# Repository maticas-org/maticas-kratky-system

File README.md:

# Maticas Kratky System 🌱

In this project we built a modified kratky system which consists of the usual bucket but now incorporates additional oxigenation with an oxigen pump, the idea behind this was to test the results of adding micorrizae to the water and keep it alive inside the kratky system with this additional aeration, comparisson tests still remain to be done yet, however we've got good results with our basil crop test.

### Results of the basil growing test

All the plants are showing a good root development.

And so far we've done 10 prunnings in about 2 months. It's true that we now have to develop a better concise and clear way to measure and compare results, but as far as building a system which allows plants to live with out concerning too much about taking care of the plants (5hr/month maximum) we've achived good results.

## Key features

- Capacity up to 8 plants with the current architecture for the growing system. 
- Measure ambient variables such as relative humidity and temperature, allows for extension and triggering of actions with this measurements.
- Control an AC actuator such as an oxigen pump _(We are expanding in order to control up to 3 AC actuators)._

- Local web server to monitor the conditions in the last 3 hours of operations of the device.
- Local web server available for modifying the periodicity and way the actuator works.
- Screen to display IP of the device in the local network and other desired data. 

<div style="display: flex; justify-content: center; align-items: center;">
  <div style="flex: 1; text-align: center; padding: 5px; height: auto; width: 45%;">
    
  </div>
  <div style="flex: 1; text-align: center; padding: 5px; height: auto; width: 45%;">
    
  </div>
</div>

## Notes over the development 📝

## Needed materials for replication ✅
### Structural materials

1. A pair of 20 liter containers [link to example product](https://articulo.mercadolibre.com.co/MCO-861436425-set-x-10-balde-cunete-20-litros-_JM#position=3&search_layout=stack&type=item&tracking_id=a9eae8bf-e021-4639-ab13-fa13d58bef19).

2. 8 cultivation baskets (or less depending on the space your plant needs) [link to reference product](https://www.amazon.com/Hydroponic-Plastic-Cultivation-Planting-Gardening/dp/B08R8LMF6L/ref=sr_1_2?crid=33OS09TYPPLFV&dib=eyJ2IjoiMSJ9.NfalgvycNBMZZM1CF_ESWtjJ-_G-A7rY25RSB5krQUKKu4zvjQOSep1QU8vNXbIBJZi8SxxX1UX_PGTqu9Y3c_O0HlxBX3RvG88J899UqGv6HMJnEB2_HnzHph0q5utguDc6kE3GUgI9agA3PfEJ_iiaWEtEIZAs9WypR67XA2uo8wHGvai6LVUqicH2mOItq_8Ez5xifLfuTdL25kr9XqGLHVQyb09th7wc6r4y1ZBvvjbuNm3003uHhowcbKyp5Qu8dFGKMpfdHdC23SAWrEkK7mI-vT8sbuXWG8rCJaw.tj7JQEGJlyXKRcYd60H6Gh8BUas8VBsp5r49KVKrqL0&dib_tag=se&keywords=cultivation%2Bbaskets&qid=1711304922&sprefix=cultivation%2Bbaskets%2B%2Caps%2C162&sr=8-2&th=1).

3. Air pump [example pump](https://articulo.mercadolibre.com.co/MCO-828833010-motor-acuario-bomba-aire-oxigenador-pecera-sin-ruido-acuario-_JM#is_advertising=true&position=1&search_layout=stack&type=pad&tracking_id=4d639074-c1e2-48ae-9c66-dc5a935c168f&is_advertising=true&ad_domain=VQCATCORE_LST&ad_position=1&ad_click_id=MjVmMDlmNWUtZmMyNC00NzI5LTg3YzItYTk3ZTJmMmUyZjk0).

4. Aquarium air stone diffusers [example diffuser](https://www.amazon.com/Aquarium-Cylinder-Accessories-Aquariums-Hydroponics/dp/B0B5R4DPP4/ref=sr_1_1?crid=1SMPKYZOVELAB&dib=eyJ2IjoiMSJ9.bYox5_LtqWn6su9Wdz4MGksotg5drfPjVbRpfjfV-7IkkrKw_FJmMDLzeYbfXDuNSDt3veWC0XFa6AAccKDn4vQ9qUUU_1QssylXTpPmLcpmMjAbBRaPriJj0xX9hwzNj1CgQbNfhM-tdzv_dWbigJumpz4xnGMrJDGax5xlCFdexQzCXAT5YXj7lvunnvkJHUjLtX1joVtqP0F6c_U1M5tq5ApRwxZfF3eH2JOzDfbZmkIhMfIV7i76dDQLvMg87O9z_dMmFcrkJMMKWhZCCJYrFKIK8w6_JuF3CszubyE.QtLIYJUgAqKs_8v_JvBkuVRv9JHkySblDV2VH8DHTeQ&dib_tag=se&keywords=piedra+difusora+de+ox%C3%ADgeno&qid=1711305222&sprefix=piedra+difusora+de+oxigeno%2Caps%2C150&sr=8-1).

5. 4 mt of silicone tube for air transportation a package like [this one](https://www.amazon.com/Airline-Tubing-Stones-Control-Connectors/dp/B0858ZSP7K/ref=sr_1_3_sspa?crid=3TNESZ93WISKB&dib=eyJ2IjoiMSJ9.sovKH5NJyHOsVmWs2hz6Ht_xFCxORp2X05G5TDa6q2JQL-1VMc0XH-OhBPIdIPjZ2DMqbKdpTYkqdIbC02VWXG6vzabmX_h4eCJGbAI5AEbuA0WyAUsYs2vwRpNiP3D_Uj2Xd3s59SmZShHrKvqzM49QpDzE4bv0fL98o1GpvlKIro7D_Pzl-cutH3pGB4XjRDQpezad1O4Es-3m8iUo_O30XGFjgO5_aJhEMZxsqeP4P3fVncNYsYNqrbthmLjemEVkY4FUC9LfnoOSpl9v1yswrIK7IoVrgauFSmWxGwA.nyoMq-X0ltysEeeU2XZvxWpWu1KCDNhN9zuVRrFSeos&dib_tag=se&keywords=silicone+aquarium+air+tubing&qid=1711305793&sprefix=aquarium+silicone+tub%2Caps%2C180&sr=8-3-spons&sp_csd=d2lkZ2V0TmFtZT1zcF9hdGY&psc=1) can be really usefull because contains most of the elements we would need to use like:
- 1 check valve.
- 1 T shape conector for airline tubing. 

### Hardware materials

1. ESP32 module as there are many providers of ESP32 modules and they sometimes change the distribution of the pins I would recommend buying first the ESP32 and then checking if the PCB files we have need some previous small adaptation to fit the ESP32 module you got.
2. DHT11 or DHT22 _(you tecnically can use any sensor you want)_ feel free to modify the code if needed.
3. 10 kohm resistor for the DHT11 sensor as a pull up. 

## Contributing and TODOs 🔨💻

The following tasks are tasks yet to be done:

- Expand to control up to 3 AC actuators.
- Currently in terms of this architecture diagram we lack the implementation of the insight generator, and the Decision taker module which could be replaced by a PID or other mean of control so that the variables we need to control, we can control. 

<div style="background-color: white; display: inline-block;">
    
</div>

- We are also learning on tiny ML to find new ways predictive tasks can be done in the embedded microcontroller and take better care of the plants.

- Any contribution you feel can be done we would be glad to help, any deploy you want to build we would be also happy to help. 

We are happy to help you, if you want to join or contribute to the project you can contact us in the following ways of communication that we leave below, also feel free to use the channels that github gives us.

## License Notice ⚖️

This project is licensed under two different licenses for different components:

### Hardware
All hardware designs in this repository are licensed under the **CERN Open Hardware Licence Version 2 - Strongly Reciprocal (CERN-OHL-S-2.0)**. 

You may use, study, modify, share, and distribute the hardware designs under the terms of the CERN-OHL-S-2.0. The full license text can be found in the `LICENSE.CERN-OHL-v2-Strongly-Reciprocal` file.

### Software
All software in this repository is licensed under the **GNU General Public License Version 3.0 (GPL-3.0)**.

You may use, modify, and distribute the software under the terms of the GPL-3.0. The full license text can be found in the `LICENSE.GPLv3` file.

---

**CERN Open Hardware Licence Version 2 - Strongly Reciprocal (CERN-OHL-S-2.0)**

Licensed under the CERN-OHL-S-2.0. You may obtain a copy of the License at [CERN-OHL-S-2.0 License](https://www.ohwr.org/project/cernohl/wikis/Documents/CERN-OHL-version-2).

**GNU General Public License Version 3.0 (GPL-3.0)**

Licensed under the GPL-3.0. You may obtain a copy of the License at [GPL-3.0 License](https://www.gnu.org/licenses/gpl-3.0.en.html).

---

Please refer to these licenses for details on your rights and responsibilities when using, modifying, and distributing components of this project.

## Acknowledgments 🤝🫂

Thanks a lot to Sergio Colmenares _(our expert in electronic engineering)_ for the testing, development and support with the electronics of this project along with the 3D box design for the protection of the electronics, without you this truly could not have been possible. The ideas and dedication you brought are amazing and hope to continue with this parthership :D.

_this box by Sergio will be available soon in this repository_.

And last but not least at all thanks to Universidad del Rosario, particularly to the EICT team Nicolás Castiblanco, Katherine Escamilla, Julian for providing help on the ideation, PCB manufacturing and soldering, debugging, materials, good conversation and all the good times shared on the process you are great friends and support <3.      
Thanks to Rafael Mendez our Dean for facilitating all the space for constructing the project, the resources, trust and visibility that keeps us connecting with the right people and ideas, you are an example for us we want to follow <3.

## Donate 💸

If you have found this project helpful or if you think it is a good precedent you can support the development of Maticas by donating here:

<p align="center"><a href='https://www.buymeacoffee.com/DaveAlsina' target='_blank'></p>

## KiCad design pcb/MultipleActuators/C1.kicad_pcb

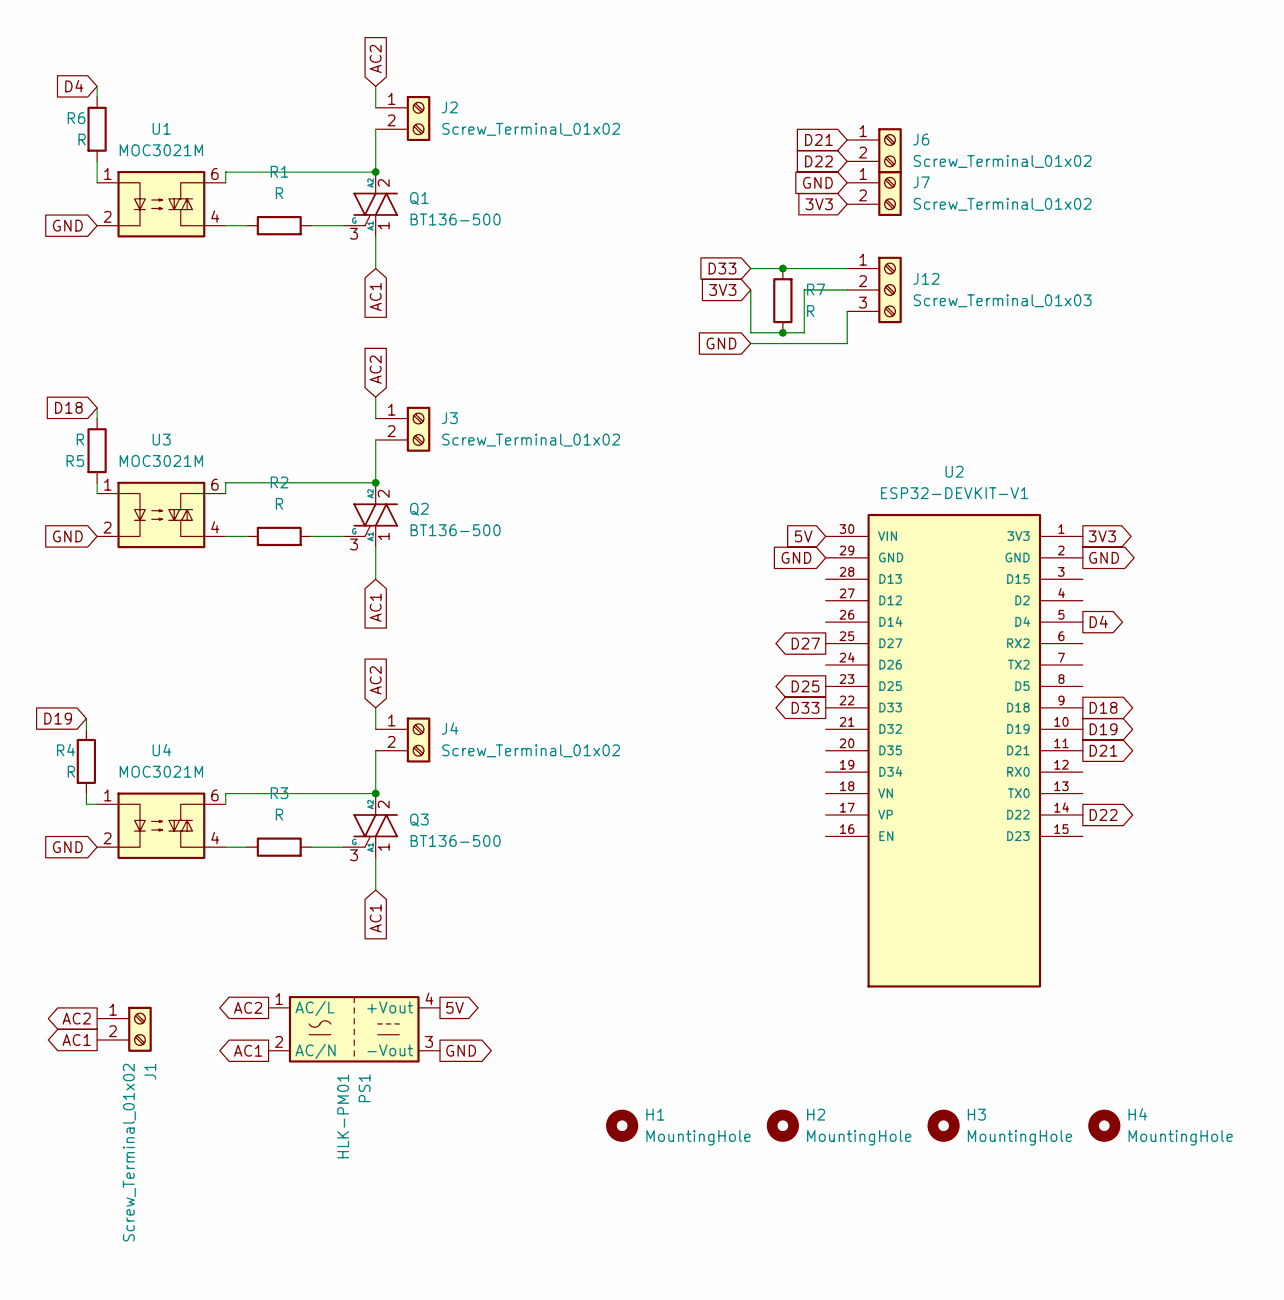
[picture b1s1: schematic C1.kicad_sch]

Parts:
H1, H2, H3, H4: MountingHole; MountingHole_3mm_Pad
J1, J2, J3, J4, J6, J7: Screw_Terminal_01x02; TerminalBlock_Altech_AK300-2_P5.00mm
J12: Screw_Terminal_01x03; TerminalBlock_Altech_AK300-3_P5.00mm
PS1: HLK-PM01; Converter_ACDC_Hi-Link_HLK-PMxx
Q1, Q2, Q3: BT136-500; TO-220-3_Vertical
R1, R2, R3, R4, R5, R6, R7: R; R_Axial_DIN0207_L6.3mm_D2.5mm_P2.54mm_Vertical
U1, U3, U4: MOC3021M; DIP-6_W7.62mm
U2: ESP32-DEVKIT-V1; MODULE_ESP32_DEVKIT_V1

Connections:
3V3: J7.2, J12.2, R7.1, U2.1 (3V3); also elsewhere on the board
5V: PS1.4 (+Vout), U2.30 (VIN)
AC1: J1.2, PS1.2 (AC/N), Q1.1 (A1), Q2.1 (A1), Q3.1 (A1)
AC2: J1.1, J2.1, J3.1, J4.1, PS1.1 (AC/L)
D4: R6.1, U2.5 (D4)
D18: R5.1, U2.9 (D18)
D19: R4.1, U2.10 (D19)
D21: J6.1, U2.11 (D21)
D22: J6.2, U2.14 (D22)
D25: U2.23 (D25)
D27: U2.25 (D27)
D33: J12.1, R7.2, U2.22 (D33); also elsewhere on the board
GND: J7.1, J12.3, PS1.3 (-Vout), U1.2, U2.2 (GND), U2.29 (GND), U3.2, U4.2
unnamed: J2.2, Q1.2 (A2), U1.6
unnamed: J3.2, Q2.2 (A2), U3.6
unnamed: J4.2, Q3.2 (A2), U4.6
unnamed: Q1.3 (G), R1.2
unnamed: Q2.3 (G), R2.2
unnamed: Q3.3 (G), R3.2
unnamed: R1.1, U1.4
unnamed: R2.1, U3.4
unnamed: R3.1, U4.4
unnamed: R4.2, U4.1
unnamed: R5.2, U3.1
unnamed: R6.2, U1.1

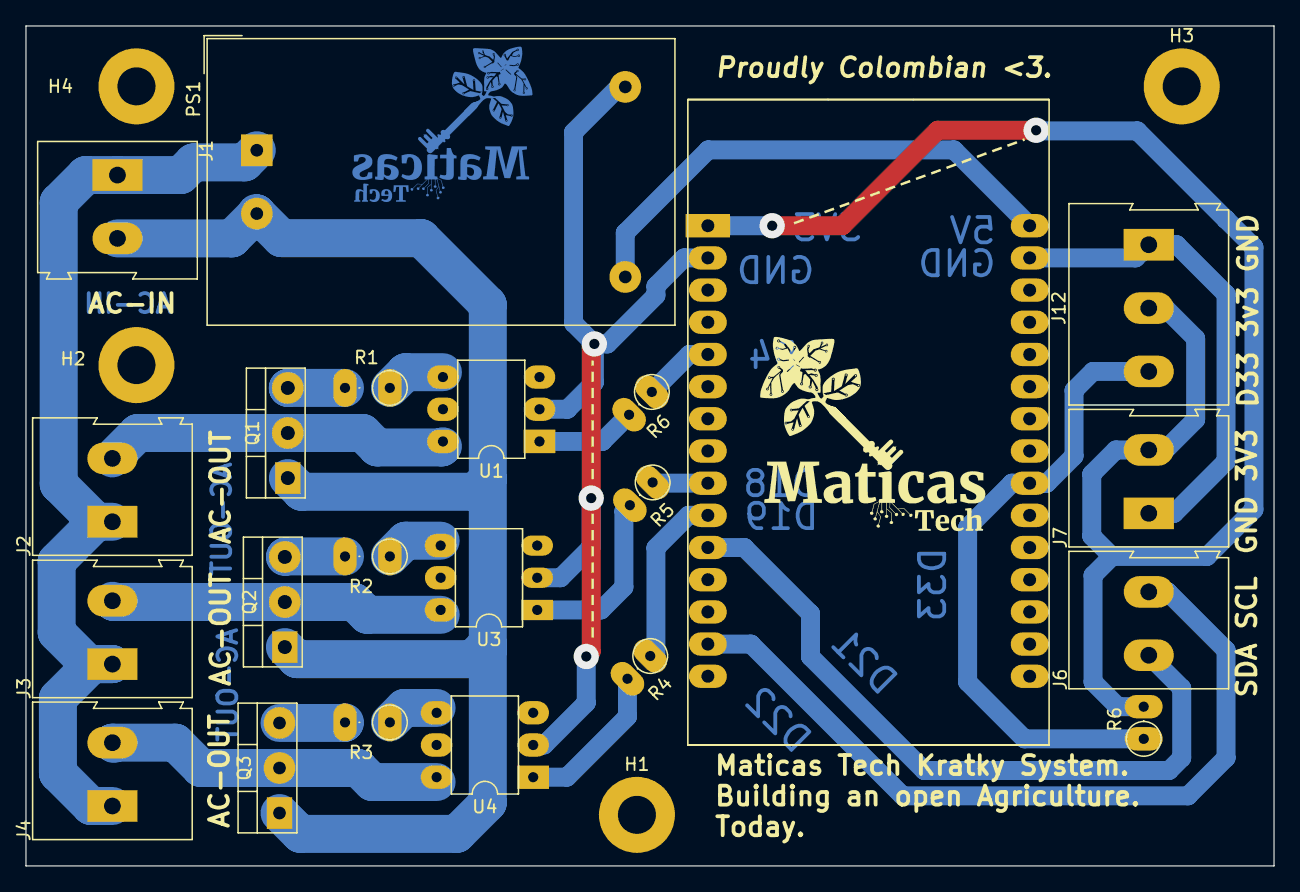
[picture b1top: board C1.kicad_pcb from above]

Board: 2 copper layers, 98.5 x 66.3 mm, 26 parts (0 on the bottom side), 23 nets.

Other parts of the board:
R6#2: R; R_Axial_DIN0207_L6.3mm_D2.5mm_P2.54mm_Vertical

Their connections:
3V3: R6#2.2; also elsewhere on the board
D33: R6#2.1; also elsewhere on the board

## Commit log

2024-02-15 Create upload_files
2024-02-16 Add kicad project
2024-03-24 Started a decent readme file
2024-03-24 advanced over readme
2024-03-24 last touches over the docs
2024-03-24 done documenting
2024-03-24 finished
2024-03-29 showing results on readme
2024-05-02 Update
    Refactor so that 2 code versions are available, the arduino flavour and the micropython flavour.
2024-05-02 Create
    Created the arduino version of the project from micropython, still lacks some features micropython has but incorportates an updated version which allows for multiple output use, for example now can u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
2024-05-02 Update
    Added the new PCB version and refactored "pcb" folder to allow for the two different versions of the pcb, the multiple output PCB is for a single layer PCB with some tricks.
2024-05-11 bugfix, there was a mistake when storing settings from the http that was mapping all the outputs to pin 0, now it uses the previous pins instead of replacing them with constant cero
2024-06-11 add dependencies on the readme
2024-06-13 Create base-design.html
    Add the base design of one view of the page so that debugging is more confortable
2024-06-13 Update InternetRTC.cpp
    updated arithmetics around offset use so that now is precise
2024-06-13 Update HtmlPages.h
    Page aesthetics ready are way better than before
2024-06-13 Update
    Updated code to allow for a maximum number of retries and a wait_time between retries
2024-06-13 Update
    now credentials are stored in the preferences storage space, so the previous functions needed to be updated for proper interfacing with previous code
2024-06-13 Update HtmlPages.h
    Added the update wifi config view, which allows for input of an SSID and a SSID_PASSWORD for when ever the ESP cannot connect to the wifi or does not find credentials to log in.
2024-06-13 Update
    now handles the logic for connecting a new esp32 (with no wifi credentials associated)
2024-06-13 Update
    allows for mDNS use when working as AP, but when connecting to router the mDNS does not work any longer, tried also to add use of static IP when connecting to WIFI and works but it seems to conflict 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
2024-06-13 Update secrets.h
    Default credentials
2024-06-17 Update secrets.h
    added logo pmb
2024-06-17 Update HandleWifi.h
    updated function so that retrieves bool which allows for better mangement of page server
2024-06-17 Update HtmlPages.h
    Titulos y logo de páginas actualizados
2024-06-17 Update main.ino
    Se añade lógica de manejo de LCD
2024-06-22 Create LICENSE
2024-06-22 Create License
    license for hardware development
2024-06-22 update
    moved licenses names
2024-06-22 Update
    now this adds the HLK-PM01 so that this can have it's own AC-DC adapter built in, and has way more comfortable connection cable management inside a box. Next iterations will be replacing the connecto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
2024-06-22 Update README.md
    Added license notice to the readme
